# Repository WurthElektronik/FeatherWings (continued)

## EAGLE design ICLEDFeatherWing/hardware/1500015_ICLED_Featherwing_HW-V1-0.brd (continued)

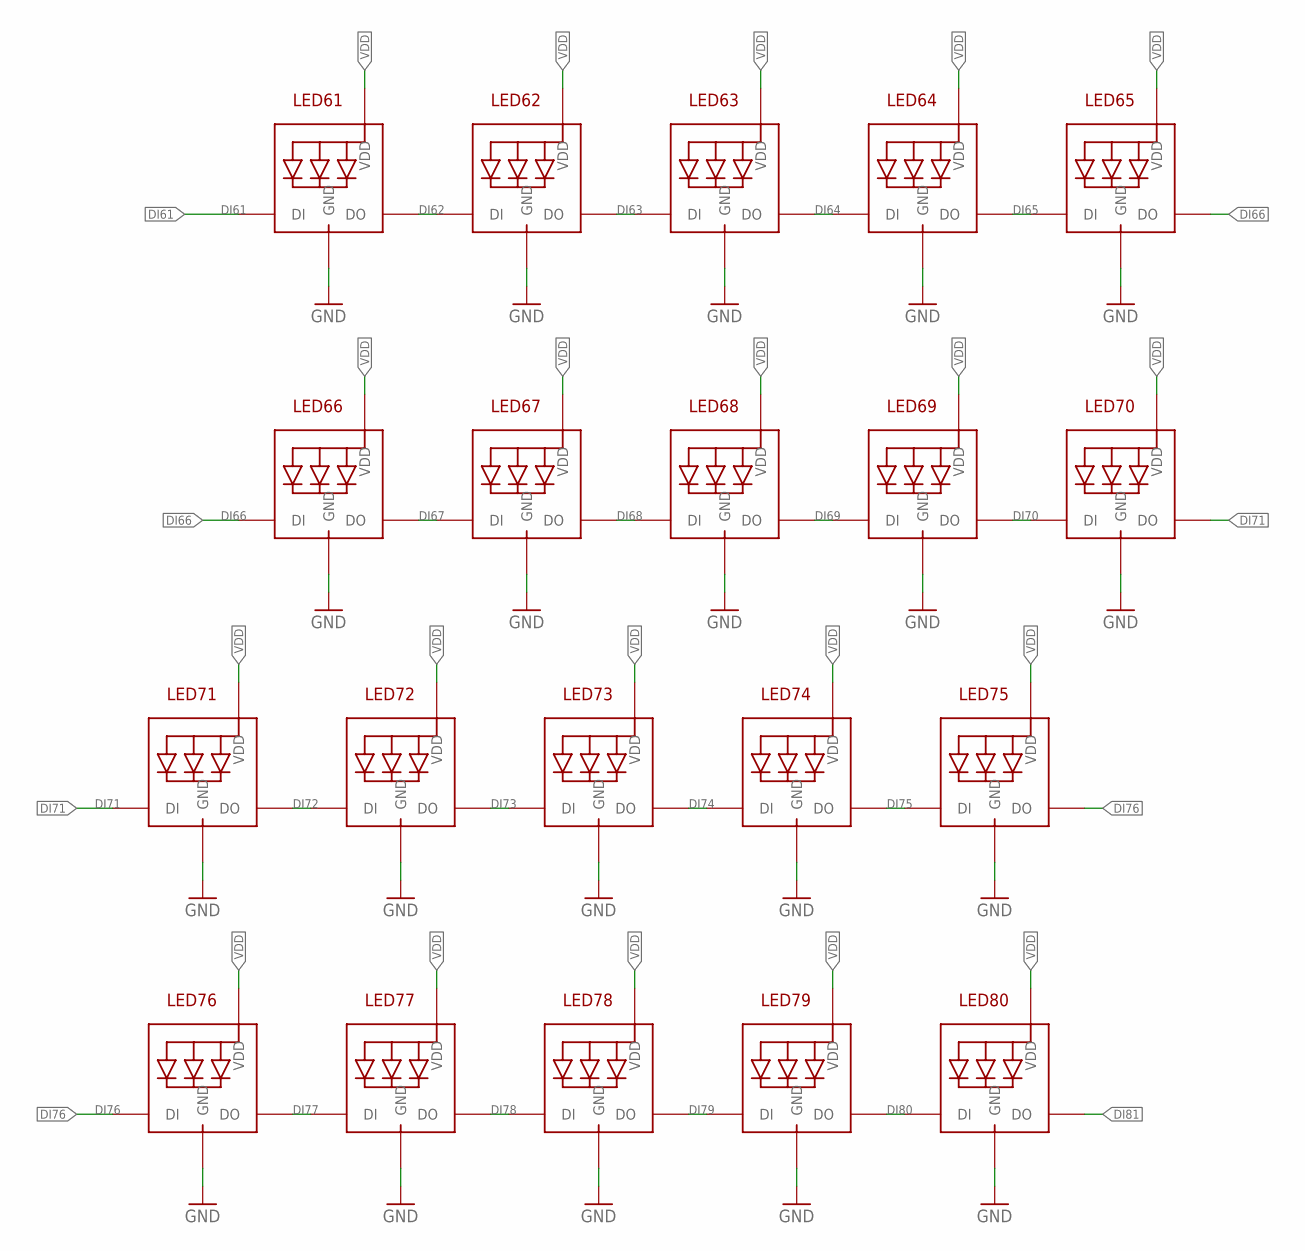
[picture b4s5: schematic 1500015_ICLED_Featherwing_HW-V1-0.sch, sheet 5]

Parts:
LED61, LED62, LED63, LED64, LED65, LED66, LED67, LED68, LED69, LED70, LED71, LED72, LED73, LED74, LED75, LED76, LED77, LED78, LED79, LED80: 1312020030000; 1312020030000_FWANGEPASST

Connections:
DI61: LED61.3-DIN (DI); also elsewhere on the board
DI62: LED61.1-DOUT (DO), LED62.3-DIN (DI)
DI63: LED62.1-DOUT (DO), LED63.3-DIN (DI)
DI64: LED63.1-DOUT (DO), LED64.3-DIN (DI)
DI65: LED64.1-DOUT (DO), LED65.3-DIN (DI)
DI66: LED65.1-DOUT (DO), LED66.3-DIN (DI)
DI67: LED66.1-DOUT (DO), LED67.3-DIN (DI)
DI68: LED67.1-DOUT (DO), LED68.3-DIN (DI)
DI69: LED68.1-DOUT (DO), LED69.3-DIN (DI)
DI70: LED69.1-DOUT (DO), LED70.3-DIN (DI)
DI71: LED70.1-DOUT (DO), LED71.3-DIN (DI)
DI72: LED71.1-DOUT (DO), LED72.3-DIN (DI)
DI73: LED72.1-DOUT (DO), LED73.3-DIN (DI)
DI74: LED73.1-DOUT (DO), LED74.3-DIN (DI)
DI75: LED74.1-DOUT (DO), LED75.3-DIN (DI)
DI76: LED75.1-DOUT (DO), LED76.3-DIN (DI)
DI77: LED76.1-DOUT (DO), LED77.3-DIN (DI)
DI78: LED77.1-DOUT (DO), LED78.3-DIN (DI)
DI79: LED78.1-DOUT (DO), LED79.3-DIN (DI)
DI80: LED79.1-DOUT (DO), LED80.3-DIN (DI)
DI81: LED80.1-DOUT (DO); also elsewhere on the board
GND: LED61.4-GND (GND), LED62.4-GND (GND), LED63.4-GND (GND), LED64.4-GND (GND), LED65.4-GND (GND), LED66.4-GND (GND), LED67.4-GND (GND), LED68.4-GND (GND), LED69.4-GND (GND), LED70.4-GND (GND), LED71.4-GND (GND), LED72.4-GND (GND), LED73.4-GND (GND), LED74.4-GND (GND), LED75.4-GND (GND), LED76.4-GND (GND), LED77.4-GND (GND), LED78.4-GND (GND), LED79.4-GND (GND), LED80.4-GND (GND); also elsewhere on the board
VDD: LED61.2-VDD (VDD), LED62.2-VDD (VDD), LED63.2-VDD (VDD), LED64.2-VDD (VDD), LED65.2-VDD (VDD), LED66.2-VDD (VDD), LED67.2-VDD (VDD), LED68.2-VDD (VDD), LED69.2-VDD (VDD), LED70.2-VDD (VDD), LED71.2-VDD (VDD), LED72.2-VDD (VDD), LED73.2-VDD (VDD), LED74.2-VDD (VDD), LED75.2-VDD (VDD), LED76.2-VDD (VDD), LED77.2-VDD (VDD), LED78.2-VDD (VDD), LED79.2-VDD (VDD), LED80.2-VDD (VDD); also elsewhere on the board

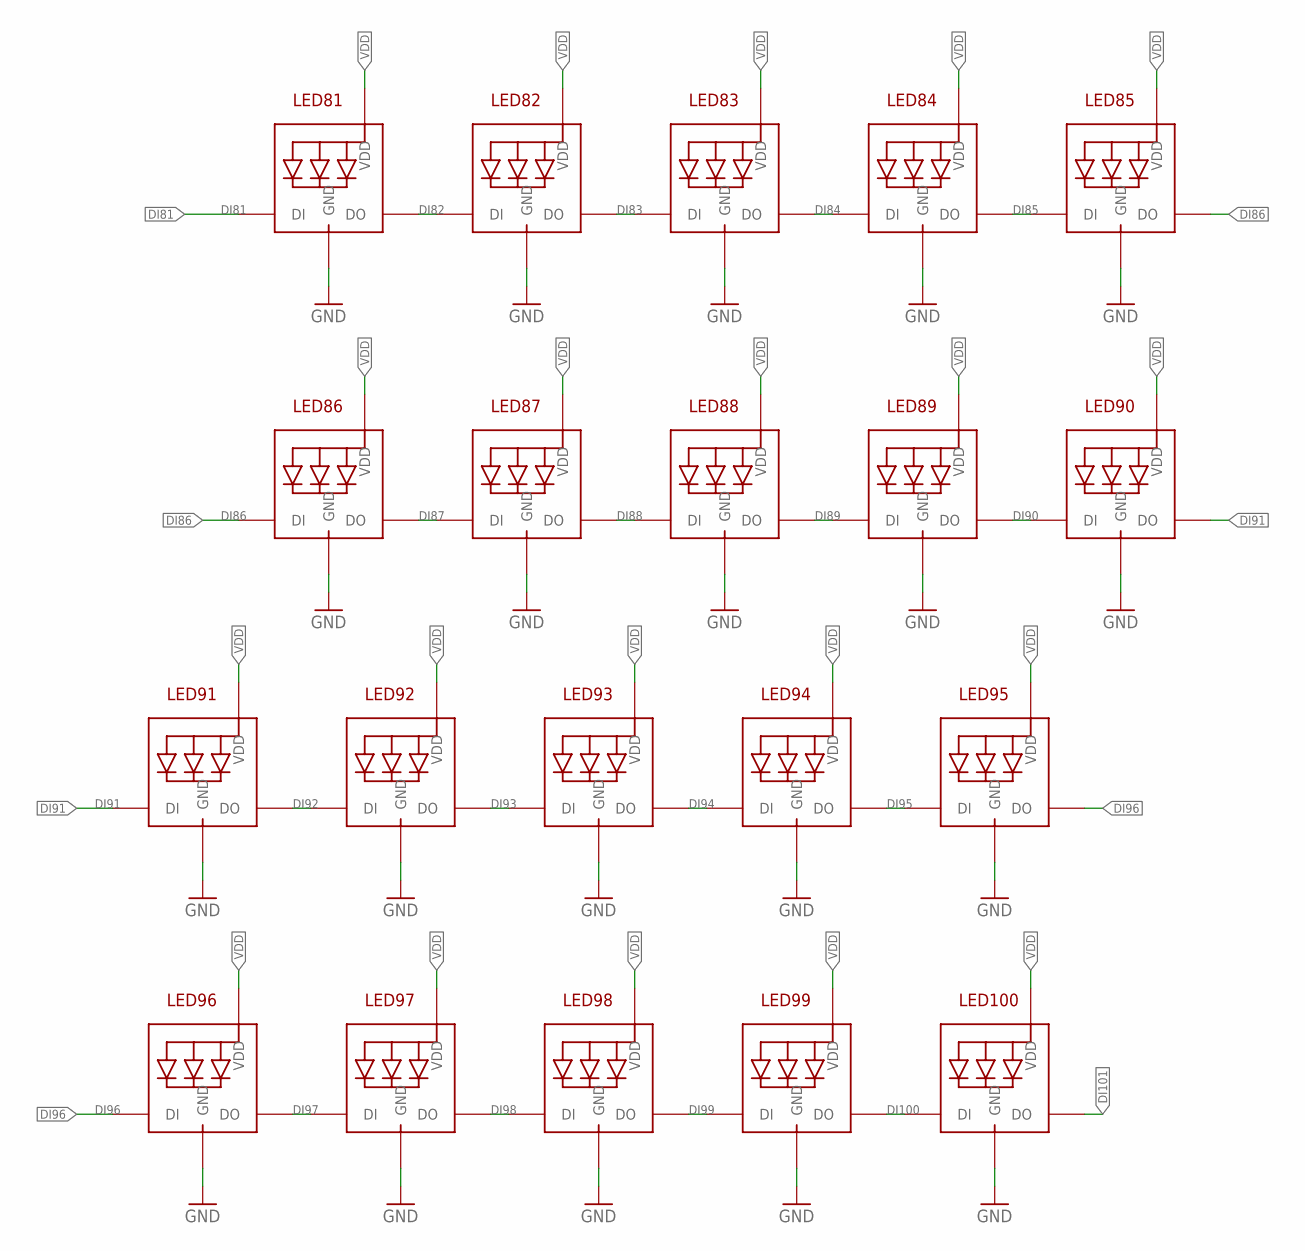
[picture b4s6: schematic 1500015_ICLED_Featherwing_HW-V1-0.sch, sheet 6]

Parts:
LED81, LED82, LED83, LED84, LED85, LED86, LED87, LED88, LED89, LED90, LED91, LED92, LED93, LED94, LED95, LED96, LED97, LED98, LED99, LED100: 1312020030000; 1312020030000_FWANGEPASST

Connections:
DI81: LED81.3-DIN (DI); also elsewhere on the board
DI82: LED81.1-DOUT (DO), LED82.3-DIN (DI)
DI83: LED82.1-DOUT (DO), LED83.3-DIN (DI)
DI84: LED83.1-DOUT (DO), LED84.3-DIN (DI)
DI85: LED84.1-DOUT (DO), LED85.3-DIN (DI)
DI86: LED85.1-DOUT (DO), LED86.3-DIN (DI)
DI87: LED86.1-DOUT (DO), LED87.3-DIN (DI)
DI88: LED87.1-DOUT (DO), LED88.3-DIN (DI)
DI89: LED88.1-DOUT (DO), LED89.3-DIN (DI)
DI90: LED89.1-DOUT (DO), LED90.3-DIN (DI)
DI91: LED90.1-DOUT (DO), LED91.3-DIN (DI)
DI92: LED91.1-DOUT (DO), LED92.3-DIN (DI)
DI93: LED92.1-DOUT (DO), LED93.3-DIN (DI)
DI94: LED93.1-DOUT (DO), LED94.3-DIN (DI)
DI95: LED94.1-DOUT (DO), LED95.3-DIN (DI)
DI96: LED95.1-DOUT (DO), LED96.3-DIN (DI)
DI97: LED96.1-DOUT (DO), LED97.3-DIN (DI)
DI98: LED97.1-DOUT (DO), LED98.3-DIN (DI)
DI99: LED98.1-DOUT (DO), LED99.3-DIN (DI)
DI100: LED99.1-DOUT (DO), LED100.3-DIN (DI)
DI101: LED100.1-DOUT (DO); also elsewhere on the board
GND: LED81.4-GND (GND), LED82.4-GND (GND), LED83.4-GND (GND), LED84.4-GND (GND), LED85.4-GND (GND), LED86.4-GND (GND), LED87.4-GND (GND), LED88.4-GND (GND), LED89.4-GND (GND), LED90.4-GND (GND), LED91.4-GND (GND), LED92.4-GND (GND), LED93.4-GND (GND), LED94.4-GND (GND), LED95.4-GND (GND), LED96.4-GND (GND), LED97.4-GND (GND), LED98.4-GND (GND), LED99.4-GND (GND), LED100.4-GND (GND); also elsewhere on the board
VDD: LED81.2-VDD (VDD), LED82.2-VDD (VDD), LED83.2-VDD (VDD), LED84.2-VDD (VDD), LED85.2-VDD (VDD), LED86.2-VDD (VDD), LED87.2-VDD (VDD), LED88.2-VDD (VDD), LED89.2-VDD (VDD), LED90.2-VDD (VDD), LED91.2-VDD (VDD), LED92.2-VDD (VDD), LED93.2-VDD (VDD), LED94.2-VDD (VDD), LED95.2-VDD (VDD), LED96.2-VDD (VDD), LED97.2-VDD (VDD), LED98.2-VDD (VDD), LED99.2-VDD (VDD), LED100.2-VDD (VDD); also elsewhere on the board

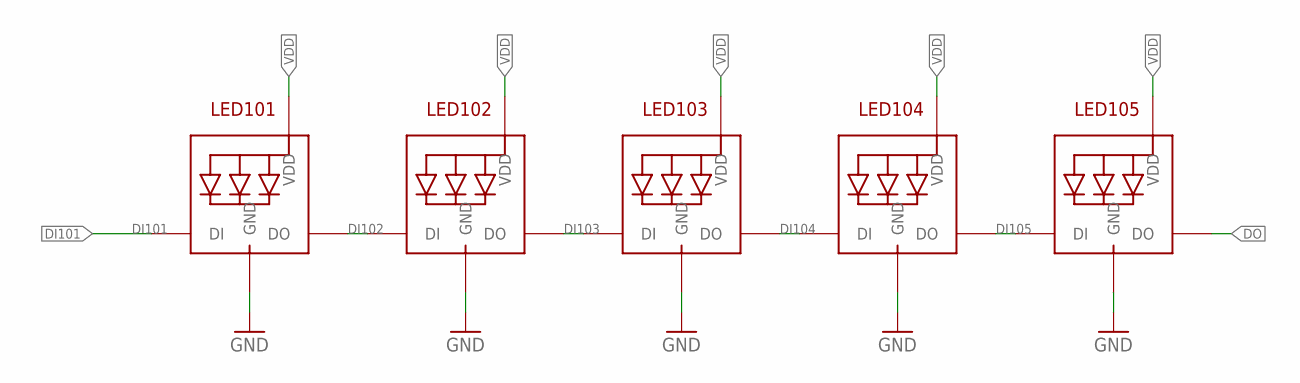
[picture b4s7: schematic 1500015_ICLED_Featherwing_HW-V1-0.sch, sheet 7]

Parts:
LED101, LED102, LED103, LED104, LED105: 1312020030000; 1312020030000_FWANGEPASST

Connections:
DI101: LED101.3-DIN (DI); also elsewhere on the board
DI102: LED101.1-DOUT (DO), LED102.3-DIN (DI)
DI103: LED102.1-DOUT (DO), LED103.3-DIN (DI)
DI104: LED103.1-DOUT (DO), LED104.3-DIN (DI)
DI105: LED104.1-DOUT (DO), LED105.3-DIN (DI)
DO: LED105.1-DOUT (DO); also elsewhere on the board
GND: LED101.4-GND (GND), LED102.4-GND (GND), LED103.4-GND (GND), LED104.4-GND (GND), LED105.4-GND (GND); also elsewhere on the board
VDD: LED101.2-VDD (VDD), LED102.2-VDD (VDD), LED103.2-VDD (VDD), LED104.2-VDD (VDD), LED105.2-VDD (VDD); also elsewhere on the board

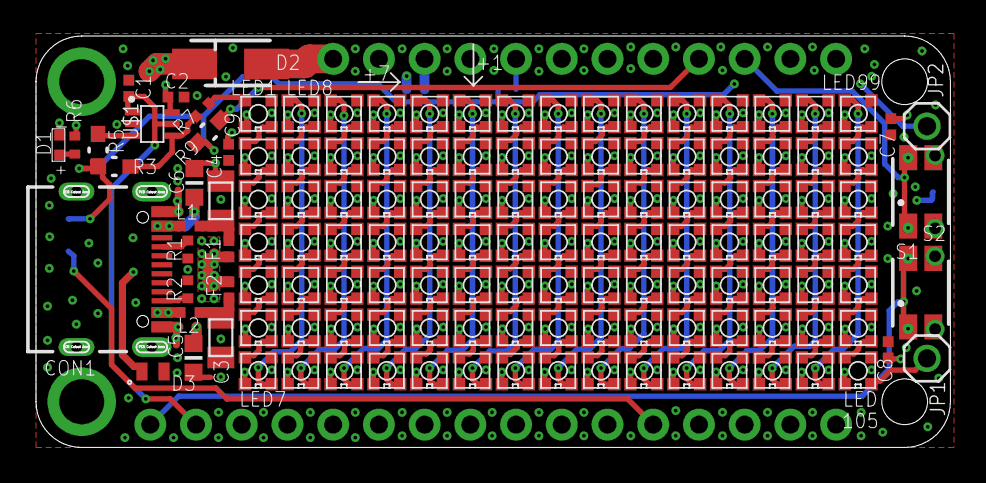
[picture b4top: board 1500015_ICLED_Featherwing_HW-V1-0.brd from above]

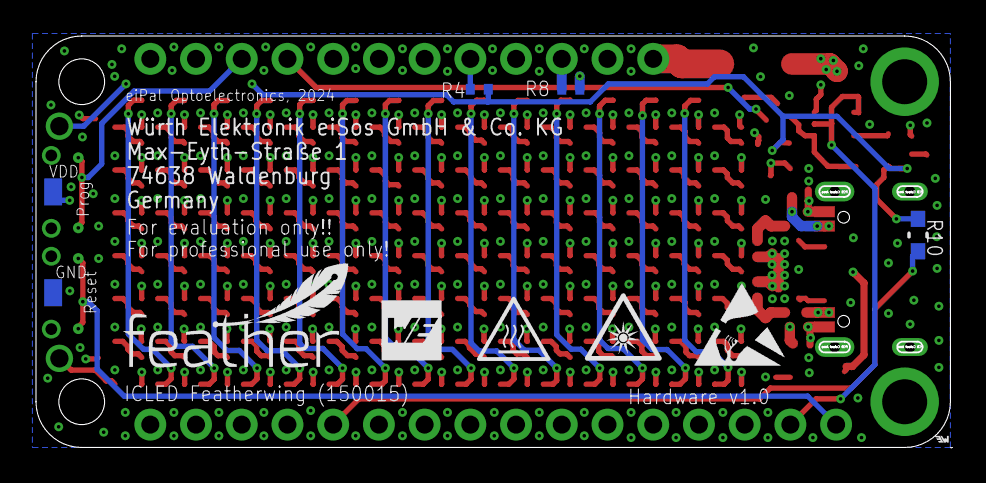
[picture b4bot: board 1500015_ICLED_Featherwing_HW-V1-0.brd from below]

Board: 4 copper layers, 50.8 x 22.9 mm, 143 parts (4 on the bottom side), 125 nets.

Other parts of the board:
U$2: OPTICAL_RADIATION
U$3: HEAT_DANGER
U$4: FEATHER_12MM

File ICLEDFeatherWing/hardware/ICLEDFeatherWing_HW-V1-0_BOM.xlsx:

Designator | Value | PACK | Height | Part number | Manufacturer | Notes | P | SPG | Total
C1, C2 | 100 nF | 0402 | 0.5 mm | 885012205037 | Würth Elektronik | SMD |  | 16V | 2
C3, C4 | 47 µF | 0805 | 0.7 mm | 885012107006 | Würth Elektronik | SMD |  | 6.3V | 2
C5, C6 | 220 nF | 0603 | 0.8 mm | 885012206125 | Wurth Elektronik | SMD |  | 50V | 2
C7, C8, C9 | 1 µF | 0402 | 0.5 mm | 885012105012 | Würth Elektronik | SMD |  | 10V | 3
CON1 | WR-COM | SMT | 2.56 mm | 629722000214 | Würth Elektronik | SMD/THT |  |  | 1
D1 | 150040RS73240 | 0402 | 0.4 mm | 150040RS73240 | Würth Elektronik | SMD |  |  | 1
D2 | SBR3U20SA-13 | SMD | 2,3 mm | SBR3U20SA-13 | Diodes Inc | SMD |  |  | 1
D3 | 824032815 | SMD | 0.5 mm | 824032815 | Würth Elektronik | SMD |  |  | 1
F1, F2 | MF-ASML050/6-2 | 0402 | 1 mm | MF-ASML050/6-2 | Bourns | SMD |  |  | 2
FC1 | 61301211121 | THT | 2.54mm | 61301211121 | Würth Elektronik | THT |  |  | 1
FC2 | 61301611121 | THT | 2.54mm | 61301611121 | Würth Elektronik | THT |  |  | 1
L1, L2 | 7427927311 | 0402 | 0.5 mm | 7427927311 | Würth Elektronik | SMD |  |  | 2
ICLED1 - ICLED105 | 1312020030000 | SMD | 0,9 mm | 1312020030000 | Würth Elektronik | SMD |  |  | 105
R1, R2 | 5K1R | 0402 | 0.35 mm | RC0402FR-075K1L | Yageo | SMD | 0.0625 W |  | 2
R3 | d.n.p. | 0603 | 0.45 mm | 560112116001 | Würth Elektronik | d.n.p. |  |  | 0
R4 | d.n.p. | 0402 | 0.35 mm | 560112110001 | Würth Elektronik | d.n.p. |  |  | 0
R5, R9 | 0R | 0603 | 0.45 mm | 560112116001 | Würth Elektronik | SMD |  |  | 2
R6 | 4K7R | 0402 | 0.35 mm | 560112110245 | Würth Elektronik | SMD | 0.1 W |  | 1
R7 | R330 | 0402 | 0.35 mm | 560112110231 | Würth Elektronik | SMD | 0.1 W |  | 1
R8 | d.n.p. | 0402 | 0.35 mm | 560112110001 | Würth Elektronik | d.n.p. |  |  | 0
R10 | d.n.p. | 0603 | 0.45 mm | 560112116001 | Würth Elektronik | d.n.p. |  |  | 0
S1, S2 | 434331013822 | SMD | 1.35 mm | 434331013822 | Würth Elektronik | SMD |  |  | 2
U$1 | TXS0101DCK | SC-70 SMD | 1 mm | TXS0101DCK | Texas Instruments | SMD |  |  | 1
PCB 150015 | - | - | - | - | - | PCB 150015 |  |  | 1
ESD Steckschaum | - | - | - | 2600110027 | Würth Elektronik | ESD-Steckschaum 50x30x10mm |  |  | 1
ESD Tüte | - | - | - | 1220205004 | Würth Elektronik | ESD-Tüte 76x127mm, silber, Zip |  |  | 1
 |  |  |  |  |  |  |  | Total | 136

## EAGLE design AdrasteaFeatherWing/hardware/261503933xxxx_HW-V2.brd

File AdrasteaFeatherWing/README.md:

# Adrastea-I FeatherWing

## Introduction

The Würth Elektronik eiSos [Adreastea-I FeatherWing](https://www.we-online.com/en/components/products/ADRASTEA-I) is a development board for the  Adrastea-I radio module. [**Adrastea-I**](https://www.we-online.com/en/components/products/ADRASTEA-I) (2615011136000) module is a compact LTE-M/NB-IoT cellular module with integrated GNSS, integrated ARM Cortex-M4 and 1MB flash memory for customer developed applications. It is fully compatible to the popular [Adafruit](https://www.adafruit.com/) [Feather line](https://www.adafruit.com/feather) of development boards and extends the feathers with Cellular IoT connectivity. 

It has an AT-style command interface on the standard UART and hence can be connected to any of the Feather microcontroller boards. The [Arduino](https://www.arduino.cc/) (C/C++) drivers and examples made available makes it easy to build a prototype to kick-start the application development.

This repository contains the [Eagle](https://www.autodesk.com/products/eagle/overview) design files for the Adreastea-I FeatherWing [PCB](hardware) as well as the [software](software) with quick start example. 

 Feel free to check our [YouTube channel](https://www.youtube.com/user/WuerthElektronik/videos) for video tutorials, hands-ons and webinars relating to our products.

## Hardware

### Description

Adrastea-I module is a compact LTE-M/NB-IoT cellular module with integrated GNSS, integrated ARM Cortex-M4 and 1MB flash memory for customer developed applications.
Based on the Sony Altair ALT1250 chipset, the Adrastea-I module provides AT-Command based multi-band configurability, enabling international multi-regional coverage in LTE Cat M1/NB1 radio access technologies.
Adrastea-I includes a fully integrated global navigation satellite system solution that supports GPS and GLONASS positioning systems.
The ARM Cortex-M4 processor is exclusively for user application software and it offers 1 MB of flash and 256 kB of RAM dedicated to this use.

Compact 13.4 mm x14.6 mm x 1.85 mm design allows the module to fit in small-size applications.
The module can be operated through one of two available cellular communication technologies:
* LTE-Cat.M or
* LTE-Cat.NB-IoT.

The module comes with the declaration of conformity (CE), is compliant to RoHS, REACh. The Adrastea-I FeatherWing module is GCF and Deutsche Telekom certified.

### Key features

| Feature | Description |
| ------- | ----------- |
|Physical Dimensions| 13.4mm x 14.6mm x 1.85mm |
|Supported Networks|  LTE-Cat.M/LTE-Cat.NB-IoT|
|LTE Supported Bands | LTE-Cat.M: B2/B3/B4/B5/B8/B12/B20/B25/B26/B28
||LTE-Cat.NB-IoT: B3/B5/B8/B20/B28|
|Module Interfaces | USIM, UART, I2C Master, SPI Master, GPIO, ADC, JTAG|
|Integrated GNSS | GPS and GLONASS| 
|Integrated User MCU |ARM Cortex-M4, 1 MB Flash Memory,256 kB RAM|
| Maximum Data Rate | LTE-Cat.M: Downlink: 300 Kbps, Uplink: 375 Kbps|
||LTE-Cat.NB-IoT: Downlink: 27.2 Kbps, Uplink: 62.5 Kbps
|3GPP Standard Compliance | 3GPP Release 13 compliant, Upgradable to Release 14|
|Output Power class| Power Class 3 (23 dBm)|
| Firmware Upgrade | Firmware upgrade over the air and USB interface|
|Supported Protocols|IPv4, IPv6, TPC/UDP SOCKET, HTTP/HTTPS, TLS/DTLS, LWM2M Client, MQTT|
|AT Commands| 3GPP TS 27.007 and 3GPP TS 27.005 AT commands, as well as Würth Elektronik eiSos enhanced AT commands|
|Operating Voltage| VDD: From 2.3 V to 4.3 V, VDD_FEM: From 3.1 V to 4.3 V|
|Temperature Range | Operation temperature: -40°C to +85°C|

Further details about the Adrastea-I radio module can be found under [we-online.de/katalog/en/Adrastea-I](https://www.we-online.com/en/components/products/ADRASTEA-I).

### Pinouts
The Adrastea FeatherWing has the following connectors,
| Connector| Description |
|----------|-------------|
|Feather Connector | Connection to other FeatherWings|
|CON1 | Micro-USB connector |
|CON2 | Li-Po Battery connector|
|CON3| Sim card connector|
|CON4| LTE RF UMRF connector|
|CON5| GNSS RF UMRF connector| 

#### Feather Connector
This is the standard set of connectors that is used across the Feather ecosystem. The table below describes the functions of each of the 28 pins as applicable to this FeatherWing.

| Pin number | Pin name | Function |
| ------- | ------- |----------------|
|   1          | <span style="text-decoration:overline">RST</span> | Not connected|
|    2          | 3V3| 3.3 V power supply|
|    3          | AREF| Not connected|
|    4          | GND| Ground|
|    5          | A0| Adrastea ADC0/GPIO1 via R16|
|    6          | A1| Adrastea ADC1/GPIO2 via R17|
|    7          | A2| Not connected|
|    8          | A3| Not connected|
|    9          | A4| Not connected|
|    10         | A5| Adrastea SPIM1_CS/GPIO40|
|    11         | SCK| Adrastea SPIM1_CLK/GPIO41|
|    12         | MOSI| Adrastea SPIM1_MOSI/GPIO38|
|    13         | MISO| Adrastea SPIM1_MISO/GPIO39|
|    14         | U0RX| Adrastea UART0 TX pin|
|    15         | U0TX| Adrastea UART0 RX pin|
|    16         | NC| Not connected|

| Pin number | Pin name | Function |
| ------- | ------- |----------------|
|    17         | SDA|I<sup>2</sup>C SDA|
|    18         | SCL|I<sup>2</sup>C SCL|
|    19         | 5| Not connected|
|    20         | 6| Adrastea WAKEUP pin|
|    21         | 9|  Not connected|
|    22         | U1TX| Not connected|
|    23         | U1RX| Not connected|
|    24         | 12| Not connected|
|    25         | 13| Not connected|
|    26         | 5V| 5 V Power supply|
|    27         | EN| Not connected|
|    28         | VBAT| Battery| 

#### CON1

Micro-USB connector that enables connection to PC via Standard USB cable. This interface can be used to power-up the device as well as access all the UART ports of the Adrastea Module.

| UART| Function|
|-------|--------|
|UART0 |Miniconsole (AT command). Only UTX and URX|
|UART1|Console Logs. Only UTX and URX|
|UART2|FW update. Full UART (inc. /CTS and /RTS)|

#### CON2
Connector CON2 is a Li-Po battery connector that allows to power board via 3.7 V Lithium-Polymer battery. VBAT is given by a charging IC with ICharge = 200 mA. ICharge can be modifed by changing R6 wich is a 5.1 k by default. A 2 k resistor for example allows a current of 500 mA. In charging mode (D9 lights up) VBAT is 4.2 V

| Pin connection | Function  |
| ------- | -------|
|    1	| VBAT |
| 2| GND |

#### CON3

Connector CON3 is a push/pull nano SIMcard holder.
| Pin connection | Function  |
| ------- | -------|
|    C1	| Voltage supply for SIMcardBAT |
| C2| SIMcard reset signal |
| C2| SIMcard clock signal |
| C2| SIMcard GND |
| C2| Not connected |
| C2| SIMcard data signal |

#### CON4
Connector CON4 (UMRF receptacle) is used to connect the LTE antenna.
| Pin connection | Function  |
| ------- | -------|
|    Inner	| RF Signal |
| Outer | GND |

#### CON5
Connector CON5 (UMRF receptacle) is used to connect the GNSS antenna.

| Pin connection | Function  |
| ------- | -------|
|    Inner	| RF Signal |
| Outer | GND |

### Push buttons

#### Push button S1
This push button is connected to the /RESET pin of the Adrastea module. Pressing this button resets the module.

#### Push button S2
This push button is connected to the WAKEUP pin of the Adrastea module. Pressing this
button allows the module to get out from sleep mode.

### LEDs
The following table shows the function of the leds included in the board.

| Name | Designator | Function  |
| ------- | -------| ----------|
| Power LED | LED1| Lights on when the board is powered up|
| Status LED | LED2 | Turns off when the module is in DH0 state|
| Charging LED | LED3 | Indicates when a battery is being charged|

### Schematics
The hardware design files including the schematics can be found in the [hardware folder](hardware).

### DISCLAIMER:
THE USE OF THE WÜRTH ELEKTRONIK EISOS DESIGN EXAMPLE / REFERENCE DESIGN IS ENTIRELY AT YOUR OWN RISK. IT IS YOUR SOLE RESPONSIBILITY TO IMPLEMENT THE DESIGN EXAMPLE / REFERENCE DESIGN WITH ALL TECHNICAL AND REGULATORY REQUIREMENTS IN YOUR APPLICATION. IT IS ALSO YOUR RESPONSIBILITY TO VERIFY THE FUNCTION AND PERFORMANCE OF YOUR DESIGN IN YOUR OWN PARTICULAR ENGINEERING AND PRODUCT ENVIRONMENT AND YOU ASSUME THE ENTIRE RISK OF DOING SO OR FAILING TO DO SO. THE WÜRTH ELEKTRONIK EISOS DESIGN EXAMPLE / REFERENCE DESIGN IS PROVIDED ON AN "AS IS" OR "AS AVAILABLE" BASIS, WITHOUT ANY WARRANTIES OF ANY KIND AND WÜRTH ELEKTRONIK EISOS DISCLAIMS ANY WARRANTIES EXPRESS OR IMPLIED, INCLUDING WITHOUT LIMITATION THE MERCHANTABILITY OR FITNESS FOR A PARTICULAR PURPOSE, USAGE OR THE NON-INFRINGEMENT OF THIRD PARTIES’ INTELLECTUAL PROPERTY RIGHTS. NO LICENSE IS GRANTED TO ANY INTELLECTUAL PROPERTY RIGHT BY WÜRTH ELEKTRONIK EISOS OR ANY THIRD PARY. UNDER NO CIRCUMSTANCES SHALL WÜRTH ELEKTRONIK EISOS BE LIABLE FOR DAMAGES INCURRED BY REASON OF OTHER SERVICES OR PRODUCTS RECEIVED THROUGH OR ADVERTISED IN CONNECTION WITH THE WÜRTH ELEKTRONIK EISOS SITE OR THE WÜRTH ELEKTRONIK EISOS DESIGN EXAMPLE / REFERENCE DESIGN. THE WÜRTH ELEKTRONIK EISOS DESIGN EXAMPLE / REFERENCE DESIGN IS SUBJECT TO CHANGE WITHOUT NOTICE.

## Software

Adreastea-I FeatherWing **software examples** can be found in the [software folder](software).

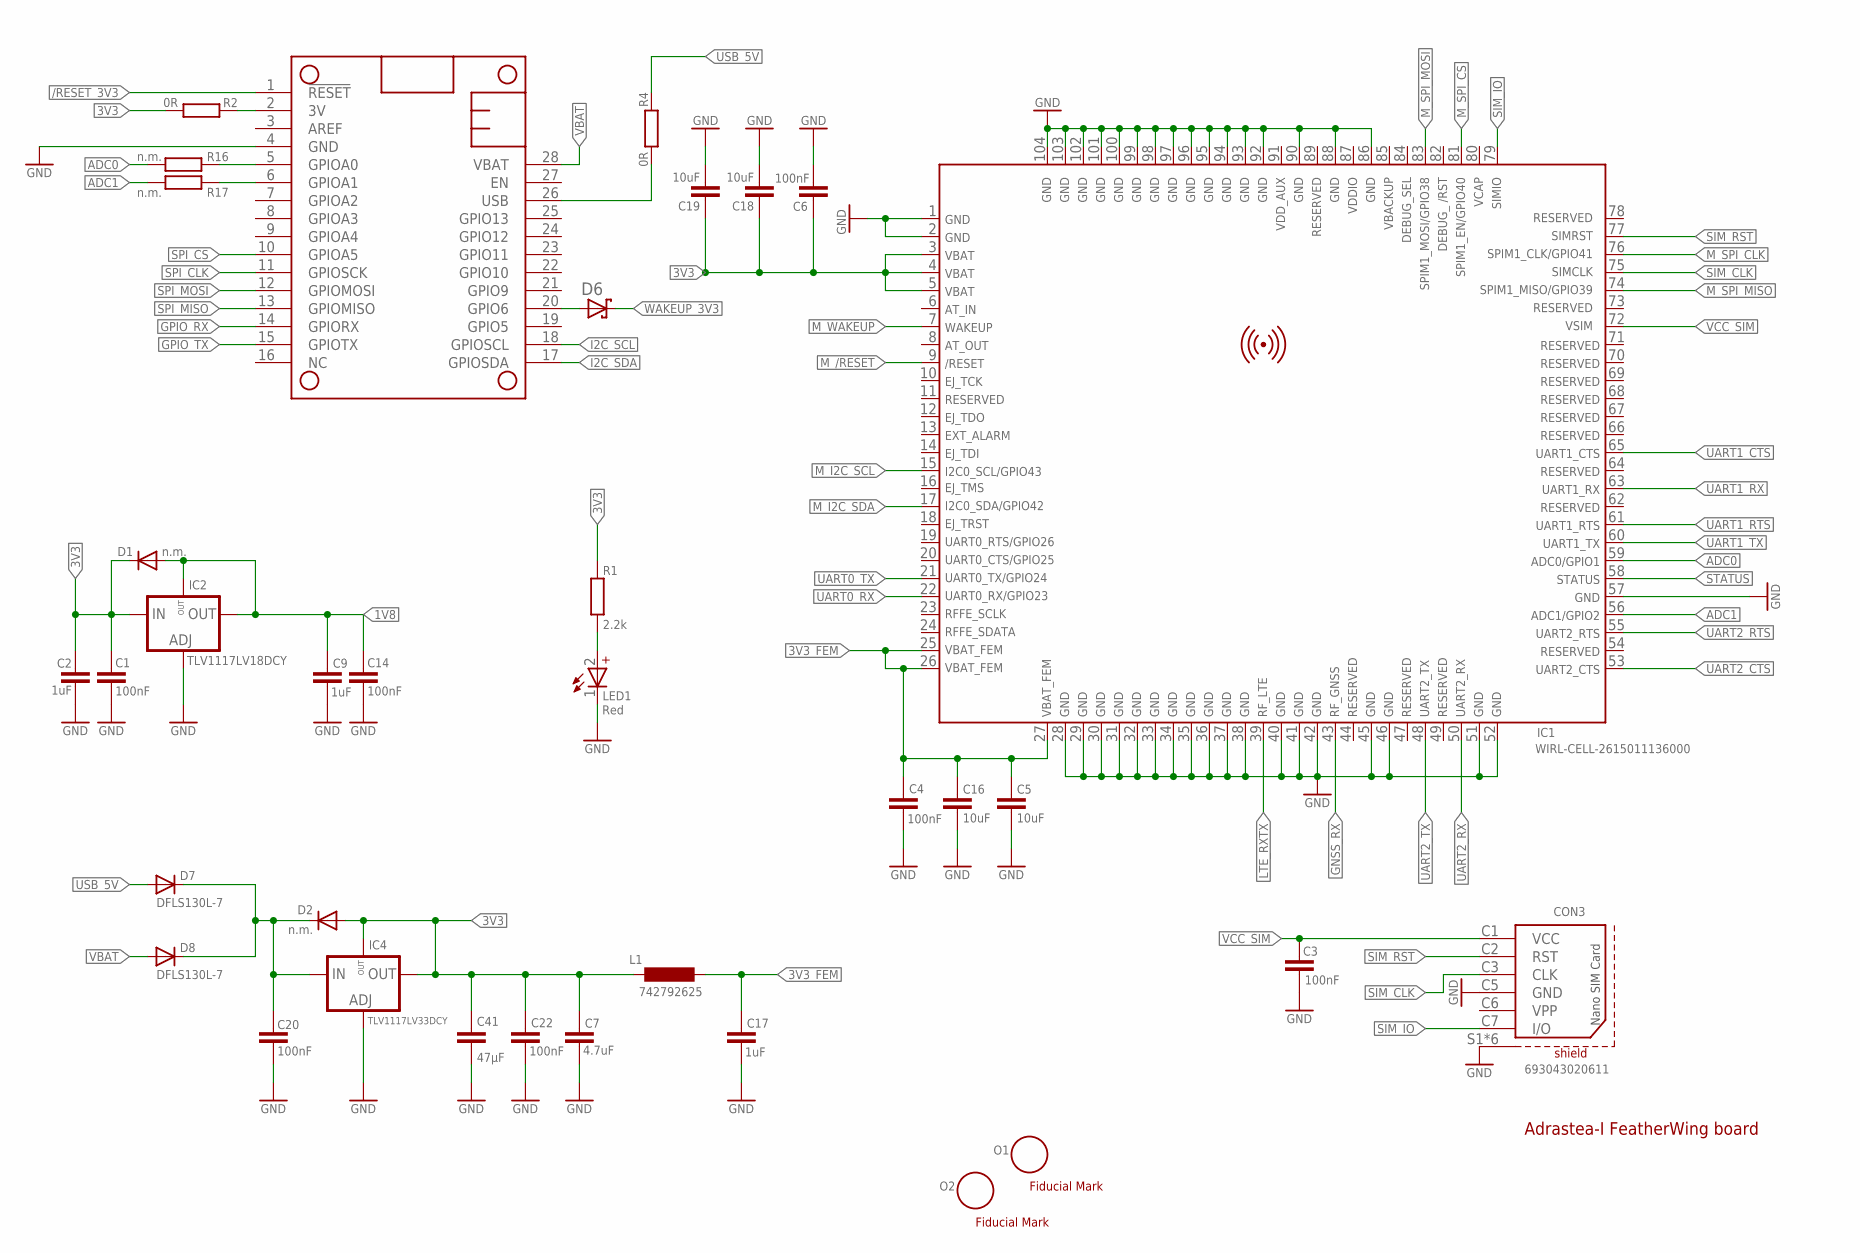
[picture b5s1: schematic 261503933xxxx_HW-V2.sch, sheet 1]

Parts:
C1, C3, C4, C6, C14, C20, C22: 100nF; C0402_IPC
C2, C9, C17: 1uF; C0402_IPC
C5, C16, C18, C19: 10uF; C0402_IPC
C7: 4.7uF; C0402_IPC
C41: 47µF; C0805
CON3: 693043020611
D1, D2: n.m.; SOT23@1
D6: BAT540402_X1-DFN1006-2; X1-DFN1006-2
D7, D8: DFLS130L-7; SOD123_POWERDI
IC1: WIRL-CELL-2615011136000
IC2: TLV1117LV18DCY; SOT223-4
IC4: TLV1117LV33DCY; SOT223-4
L1: 742792625; L0603_WE-MK
LED1: Red; WL-SMSW_1204_A
MS1: FEATHERWING_80MM
O1, O2: OPT_MARKE05; OPT_M_05
R1: 2.2k; R0402_IPC
R2, R4: 0R; R0603_IPC
R16, R17: n.m.; R0402_IPC

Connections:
1V8: C9.1, C14.2, D1.1 (A), IC2.2 (OUT), IC2.4 (OUT); also elsewhere on the board
3V: MS1.2 (3V), R2.2
3V3: C1.2, C2.1, C6.2, C7.1, C18.1, C19.1, C22.2, C41.P$1 (1), D1.3 (C), D2.1 (A), IC1.3 (VBAT), IC1.4 (VBAT), IC1.5 (VBAT), IC2.3 (IN), IC4.2 (OUT), IC4.4 (OUT), L1.1, R1.2, R2.1; also elsewhere on the board
3V3_FEM: C4.2, C5.1, C16.1, C17.1, IC1.25 (VBAT_FEM), IC1.26 (VBAT_FEM), IC1.27 (VBAT_FEM), L1.2
5V_IN: C20.2, D2.3 (C), D7.K (C), D8.K (C), IC4.3 (IN)
/RESET_3V3: MS1.1 (!RESET); also elsewhere on the board
ADC0: IC1.59 (ADC0/GPIO1), R16.1
ADC1: IC1.56 (ADC1/GPIO2), R17.1
ADC_0: MS1.5 (GPIOA0), R16.2
ADC_1: MS1.6 (GPIOA1), R17.2
FEATHER_USB: MS1.26 (USB), R4.1
GND: C1.1, C2.2, C3.2, C4.1, C5.2, C6.1, C7.2, C9.2, C14.1, C16.2, C17.2, C18.2, C19.2, C20.1, C22.1, C41.P$2 (2), CON3.C5 (GND), CON3.S1 (SHIELD), CON3.S2 (SHIELD), CON3.S3 (SHIELD), CON3.S4 (SHIELD), CON3.S5 (SHIELD), CON3.S6 (SHIELD), IC1.1 (GND), IC1.2 (GND), IC1.28 (GND), IC1.29 (GND), IC1.30 (GND), IC1.31 (GND), IC1.32 (GND), IC1.33 (GND), IC1.34 (GND), IC1.35 (GND), IC1.36 (GND), IC1.37 (GND), IC1.38 (GND), IC1.40 (GND), IC1.41 (GND), IC1.42 (GND), IC1.45 (GND), IC1.46 (GND), IC1.51 (GND), IC1.52 (GND), IC1.57 (GND), IC1.86 (GND), IC1.88 (GND), IC1.90 (GND), IC1.92 (GND), IC1.93 (GND), IC1.94 (GND), IC1.95 (GND), IC1.96 (GND), IC1.97 (GND), IC1.98 (GND), IC1.99 (GND), IC1.100 (GND), IC1.101 (GND), IC1.102 (GND), IC1.103 (GND), IC1.104 (GND), IC2.1 (ADJ), IC4.1 (ADJ), LED1.1 (-), MS1.4 (GND); also elsewhere on the board
GNSS_RX: IC1.43 (RF_GNSS_ANT); also elsewhere on the board
GPIO_RX: MS1.14 (GPIORX); also elsewhere on the board
GPIO_TX: MS1.15 (GPIOTX); also elsewhere on the board
I2C_SCL: MS1.18 (GPIOSCL); also elsewhere on the board
I2C_SDA: MS1.17 (GPIOSDA); also elsewhere on the board
LTE_RXTX: IC1.39 (RF_RXTX); also elsewhere on the board
M_/RESET: IC1.9 (/RESET); also elsewhere on the board
M_I2C_SCL: IC1.15 (I2C0_SCL/GPIO43); also elsewhere on the board
M_I2C_SDA: IC1.17 (I2C0_SDA/GPIO42); also elsewhere on the board
M_SPI_CLK: IC1.76 (SPIM1_CLK/GPIO41); also elsewhere on the board
M_SPI_CS: IC1.81 (SPIM1_EN/GPIO40); also elsewhere on the board
M_SPI_MISO: IC1.74 (SPIM1_MISO/GPIO39); also elsewhere on the board
M_SPI_MOSI: IC1.83 (SPIM1_MOSI/GPIO38); also elsewhere on the board
M_WAKEUP: IC1.7 (WAKEUP); also elsewhere on the board
unnamed: LED1.2 (+), R1.1
unnamed: D6.2 (A), MS1.20 (GPIO6)
SIM_CLK: CON3.C3 (CLK), IC1.75 (SIMCLK)
SIM_IO: CON3.C7 (I/O), IC1.79 (SIMIO)
SIM_RST: CON3.C2 (RST), IC1.77 (SIMRST)
SPI_CLK: MS1.11 (GPIOSCK); also elsewhere on the board
SPI_CS: MS1.10 (GPIOA5); also elsewhere on the board
SPI_MISO: MS1.13 (GPIOMISO); also elsewhere on the board
SPI_MOSI: MS1.12 (GPIOMOSI); also elsewhere on the board
STATUS: IC1.58 (STATUS); also elsewhere on the board
UART0_RX: IC1.22 (UART0_RX/GPIO23); also elsewhere on the board
UART0_TX: IC1.21 (UART0_TX/GPIO24); also elsewhere on the board
UART1_CTS: IC1.65 (UART1_CTS); also elsewhere on the board
UART1_RTS: IC1.61 (UART1_RTS); also elsewhere on the board
UART1_RX: IC1.63 (UART1_RX); also elsewhere on the board
UART1_TX: IC1.60 (UART1_TX); also elsewhere on the board
UART2_CTS: IC1.53 (UART2_CTS); also elsewhere on the board
UART2_RTS: IC1.55 (UART2_RTS); also elsewhere on the board
UART2_RX: IC1.50 (UART2_RX); also elsewhere on the board
UART2_TX: IC1.48 (UART2_TX); also elsewhere on the board
USB_5V: D7.A, R4.2; also elsewhere on the board
VBAT: D8.A, MS1.28 (VBAT); also elsewhere on the board
VCC_SIM: C3.1, CON3.C1 (VCC), IC1.72 (VSIM)
WAKEUP_3V3: D6.1 (C); also elsewhere on the board

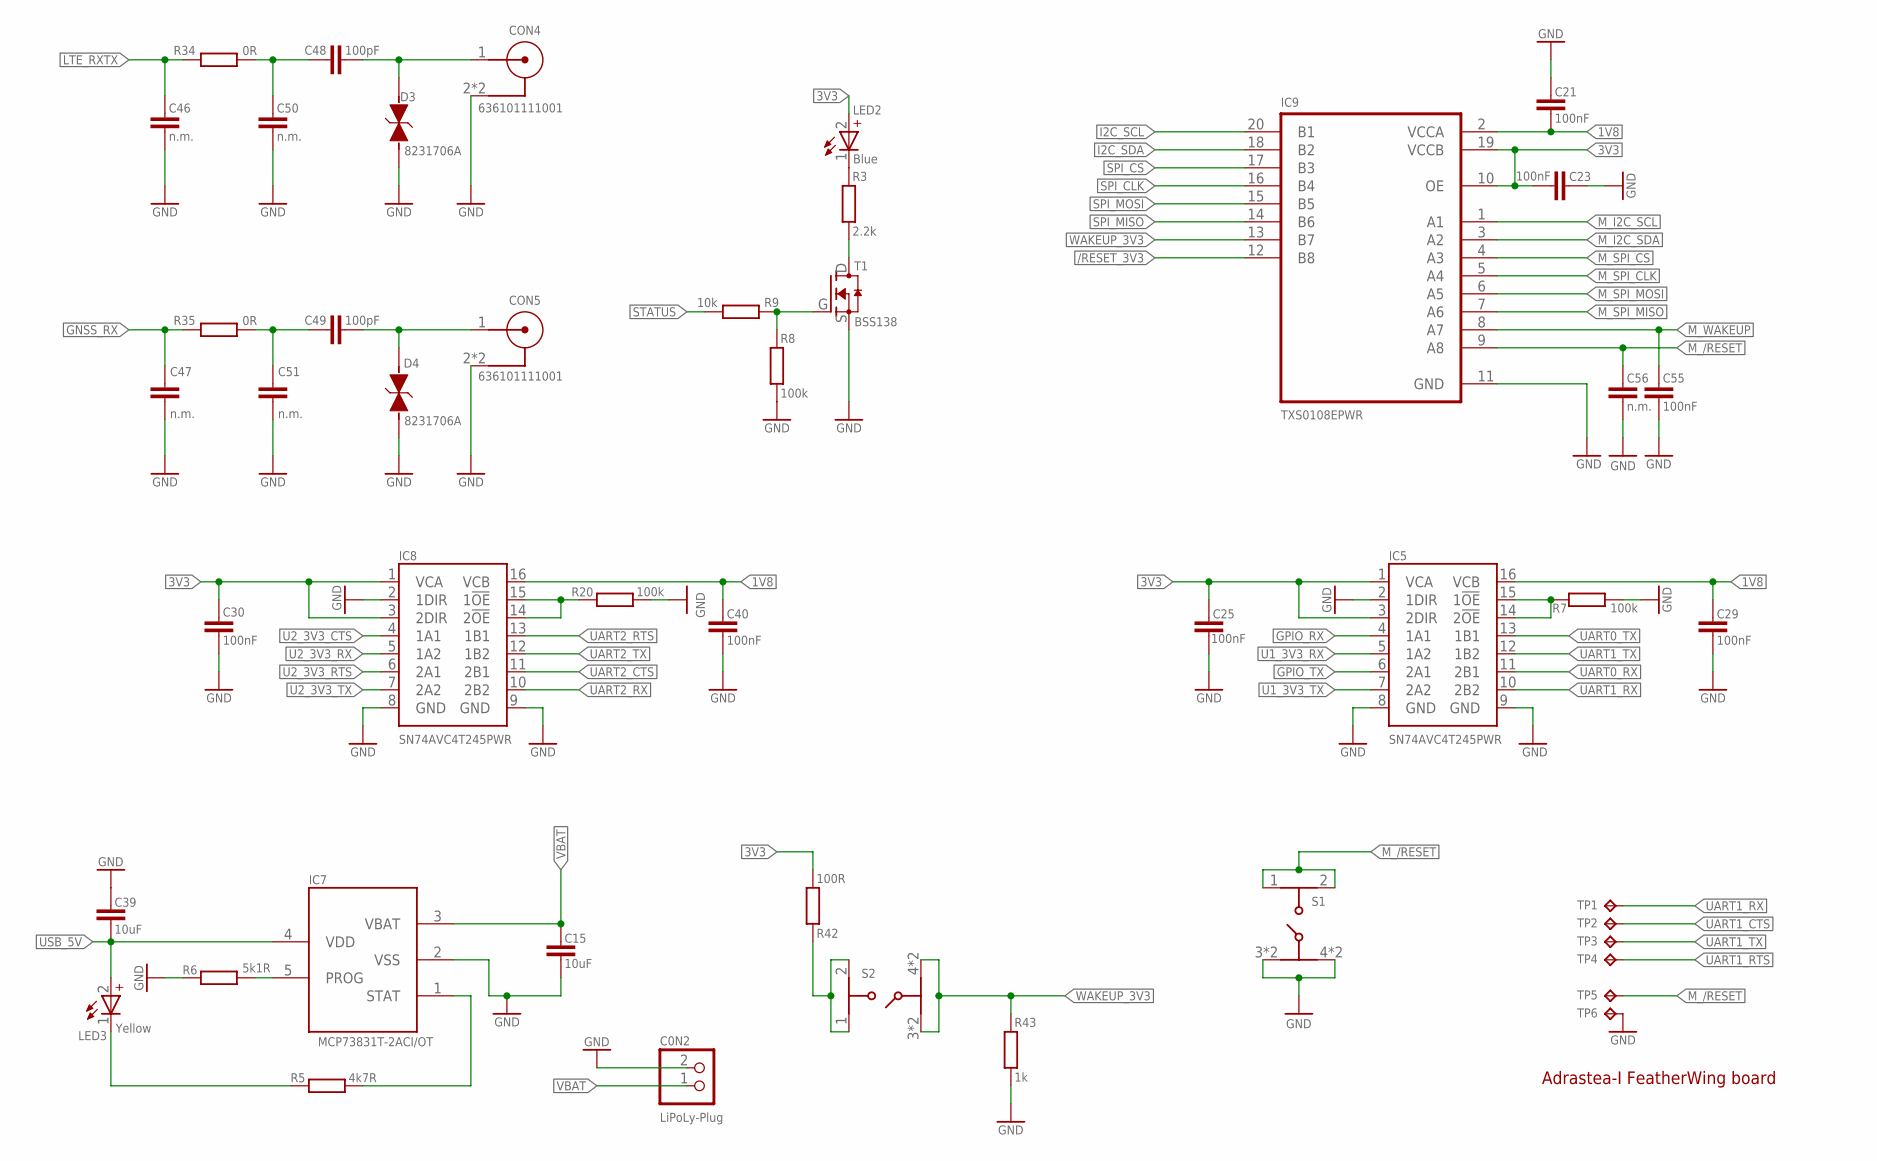
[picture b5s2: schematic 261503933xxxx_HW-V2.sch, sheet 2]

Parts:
C0N2: LiPoLy-Plug; JST-PH-2-SMT-RA-ADRASTEA-ANGEPASST
C15: 10uF; C0402_IPC
C21, C23, C25, C29, C30, C40, C55: 100nF; C0402_IPC
C39: 10uF; C0603_IPC
C46, C47, C50, C51, C56: n.m.; C0402_IPC
C48, C49: 100pF; C0402_IPC
CON4, CON5: 636101111001
D3, D4: 8231706A; WE-VE_FEMTOF_0402
IC5, IC8: SN74AVC4T245PWR; PW16(TSSOP16)
IC7: MCP73831T-2ACI/OT; SOT23-5
IC9: TXS0108EPWR; SOP65P640X120-20N
LED2: Blue; WL-SMSW_1204_A
LED3: Yellow; WL-SMSW_1204_A
R3: 2.2k; R0402_IPC
R5: 4k7R; R0402_IPC
R6: 5k1R; R0402_IPC
R7, R8, R20: 100k; R0402_IPC
R9: 10k; R0402_IPC
R34, R35: 0R; R0402_IPC
R42: 100R; R0402_IPC
R43: 1k; R0402_IPC
S1, S2: 434331013822
T1: BSS138
TP1, TP2, TP3, TP4, TP5, TP6: TP15R

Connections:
1V8: C21.1, C29.2, C40.2, IC5.16 (VCB), IC8.16 (VCB), IC9.2 (VCCA); also elsewhere on the board
3V3: C23.1, C25.2, C30.2, IC5.1 (VCA), IC5.3 (2DIR), IC8.1 (VCA), IC8.3 (2DIR), IC9.10 (OE), IC9.19 (VCCB), LED2.2 (+), R42.1; also elsewhere on the board
/RESET_3V3: IC9.12 (B8); also elsewhere on the board
GND: C0N2.2 (1), C15.2, C21.2, C23.2, C25.1, C29.1, C30.1, C39.1, C40.1, C46.1, C47.1, C50.1, C51.1, C55.1, C56.1, CON4.2, CON4.3 (2), CON5.2, CON5.3 (2), D3.2, D4.2, IC5.2 (1DIR), IC5.8 (GND), IC5.9 (GND), IC7.2 (VSS), IC8.2 (1DIR), IC8.8 (GND), IC8.9 (GND), IC9.11 (GND), R6.1, R7.2, R8.2, R20.2, R43.2, S1.3, S1.4, S1.5 (3), S1.6 (4), T1.S, TP6.P$1; also elsewhere on the board
GNSS_RX: C47.2, R35.2; also elsewhere on the board
GPIO_RX: IC5.4 (1A1); also elsewhere on the board
GPIO_TX: IC5.6 (2A1); also elsewhere on the board
I2C_SCL: IC9.20 (B1); also elsewhere on the board
I2C_SDA: IC9.18 (B2); also elsewhere on the board
LS_ISO_CTRL1: IC8.14 (2!OE), IC8.15 (1!OE), R20.1
LTE_RXTX: C46.2, R34.2; also elsewhere on the board
M_/RESET: C56.2, IC9.9 (A8), S1.1, S1.2, TP5.P$1; also elsewhere on the board
M_I2C_SCL: IC9.1 (A1); also elsewhere on the board
M_I2C_SDA: IC9.3 (A2); also elsewhere on the board
M_SPI_CLK: IC9.5 (A4); also elsewhere on the board
M_SPI_CS: IC9.4 (A3); also elsewhere on the board
M_SPI_MISO: IC9.7 (A6); also elsewhere on the board
M_SPI_MOSI: IC9.6 (A5); also elsewhere on the board
M_WAKEUP: C55.2, IC9.8 (A7); also elsewhere on the board
unnamed: LED2.1 (-), R3.1
unnamed: C49.1, CON5.1, D4.1
unnamed: C48.1, CON4.1, D3.1
unnamed: R42.2, S2.1, S2.2
unnamed: C48.2, C50.2, R34.1
unnamed: R3.2, T1.D
unnamed: C49.2, C51.2, R35.1
unnamed: R8.1, R9.2, T1.G
unnamed: LED3.1 (-), R5.1
unnamed: IC7.5 (PROG), R6.2
unnamed: IC5.14 (2!OE), IC5.15 (1!OE), R7.1
SPI_CLK: IC9.16 (B4); also elsewhere on the board
SPI_CS: IC9.17 (B3); also elsewhere on the board
SPI_MISO: IC9.14 (B6); also elsewhere on the board
SPI_MOSI: IC9.15 (B5); also elsewhere on the board
STAT: IC7.1 (STAT), R5.2
STATUS: R9.1; also elsewhere on the board
U1_3V3_RX: IC5.5 (1A2); also elsewhere on the board
U1_3V3_TX: IC5.7 (2A2); also elsewhere on the board
U2_3V3_CTS: IC8.4 (1A1); also elsewhere on the board
U2_3V3_RTS: IC8.6 (2A1); also elsewhere on the board
U2_3V3_RX: IC8.5 (1A2); also elsewhere on the board
U2_3V3_TX: IC8.7 (2A2); also elsewhere on the board
UART0_RX: IC5.11 (2B1); also elsewhere on the board
UART0_TX: IC5.13 (1B1); also elsewhere on the board
UART1_CTS: TP2.P$1; also elsewhere on the board
UART1_RTS: TP4.P$1; also elsewhere on the board
UART1_RX: IC5.10 (2B2), TP1.P$1; also elsewhere on the board
UART1_TX: IC5.12 (1B2), TP3.P$1; also elsewhere on the board
UART2_CTS: IC8.11 (2B1); also elsewhere on the board
UART2_RTS: IC8.13 (1B1); also elsewhere on the board
UART2_RX: IC8.10 (2B2); also elsewhere on the board
UART2_TX: IC8.12 (1B2); also elsewhere on the board
USB_5V: C39.2, IC7.4 (VDD), LED3.2 (+); also elsewhere on the board
VBAT: C0N2.1 (2), C15.1, IC7.3 (VBAT); also elsewhere on the board
WAKEUP_3V3: IC9.13 (B7), R43.1, S2.3, S2.4, S2.5 (3), S2.6 (4); also elsewhere on the board
